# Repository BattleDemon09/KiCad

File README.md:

# KiCad
KiCad Schematics and PCBs

Please save all KiCad work here in a relevant folder

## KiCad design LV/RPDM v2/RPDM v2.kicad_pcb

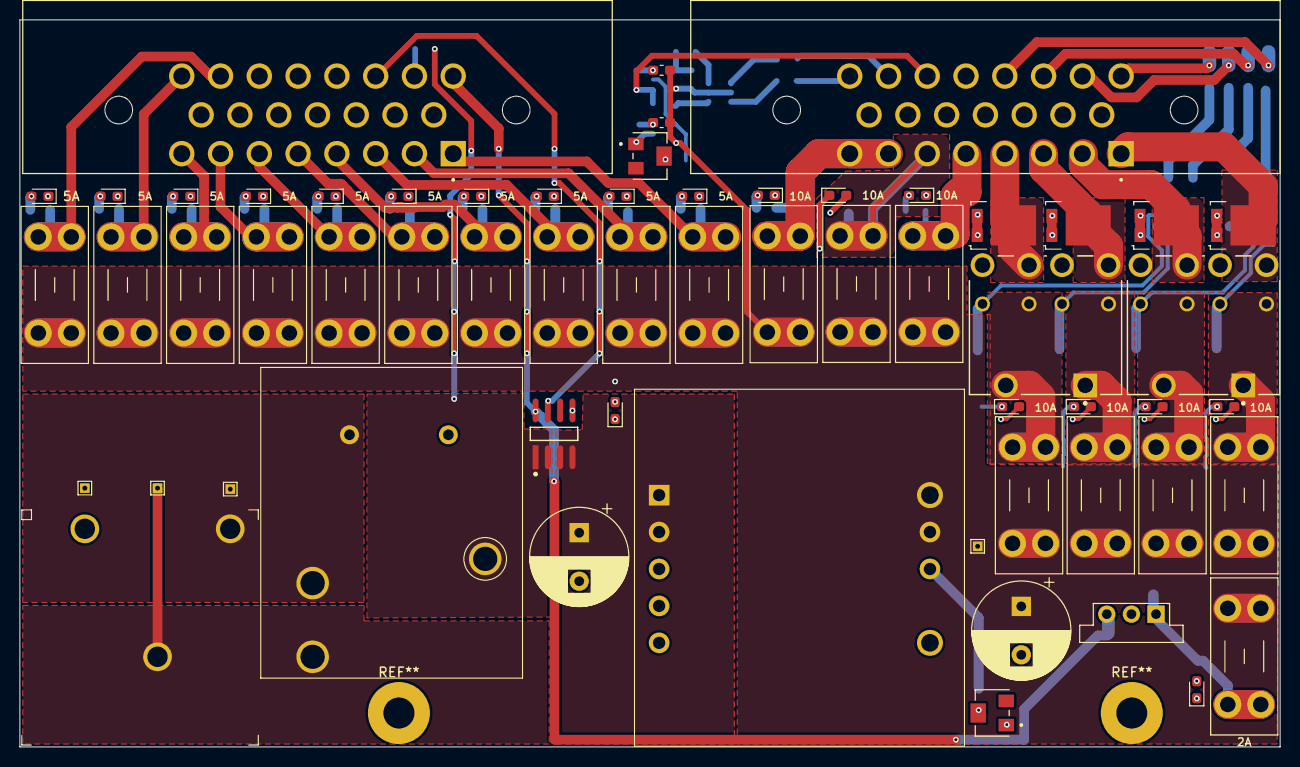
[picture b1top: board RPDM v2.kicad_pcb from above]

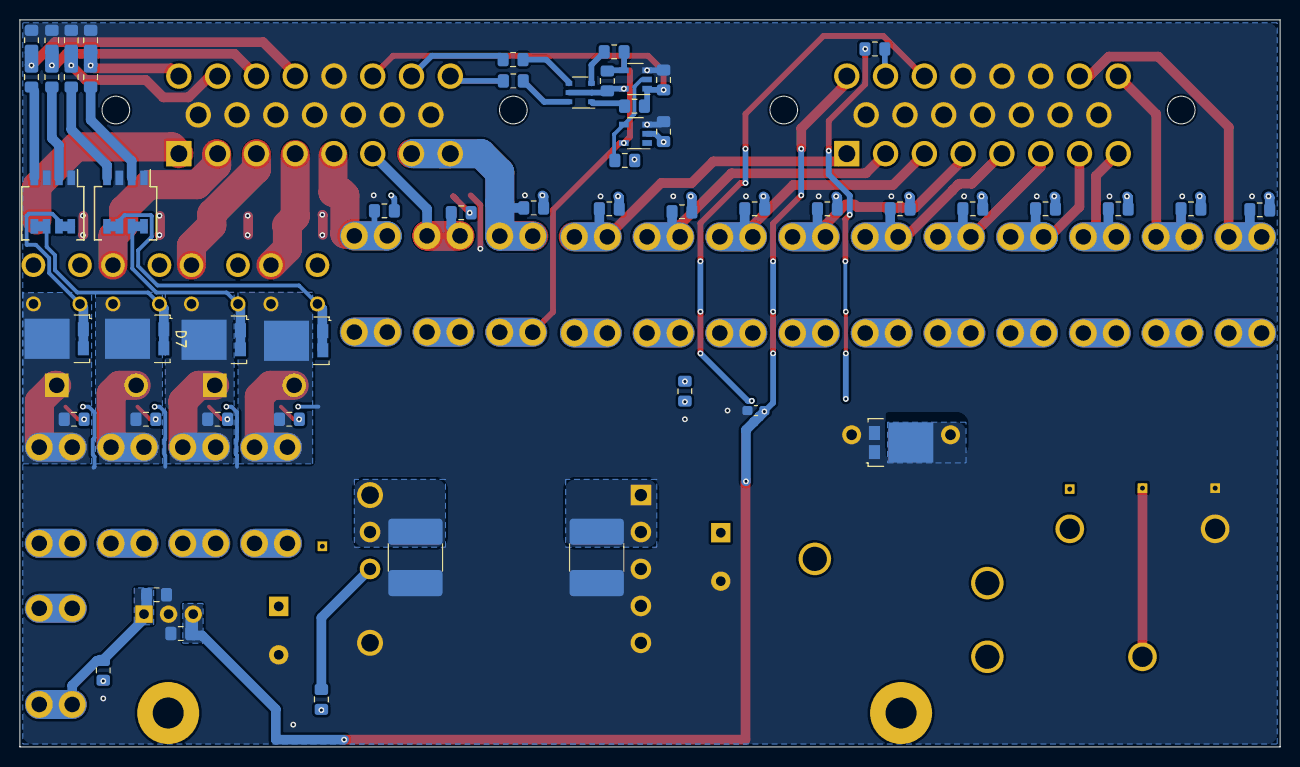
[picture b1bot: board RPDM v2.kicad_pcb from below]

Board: 2 copper layers, 130.0 x 75.0 mm, 112 parts (52 on the bottom side), 75 nets.

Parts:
C1, C3, C6: 0.1µF; C_0603_1608Metric_Pad1.05x0.95mm_HandSolder
C2: 1uF; C_0805_2012Metric_Pad1.15x1.40mm_HandSolder
C4, C5: 22µF; C_0805_2012Metric_Pad1.15x1.40mm_HandSolder
C7: 330µF; CP_Radial_D10.0mm_P5.00mm
C8, C9: 22µF; C_Murata_KCM55
C10: 330uF; CP_Radial_D10.0mm_P5.00mm
D1, D2, D3, D4, D5, D6, D7, D8, D30: D_Schottky_Flyback; TO-277_FSV10150V
D9, D10, D11, D12, D13, D14, D15, D16, D17, D18, D19, D20, D21, D22, D23, D24, D25, D26: OK_LED; D_0603_1608Metric_Pad1.05x0.95mm_HandSolder
D29: PWR_ON_LED; D_0603_1608Metric_Pad1.05x0.95mm_HandSolder
F1, F2, F3, F4, F5, F6, F7, F8, F9, F10, F11, F12, F13, F14, F15, F16, F17, F18: Fuse; Keystone_3568
J1: 24V_IN; EB167A-03-M
J2: 1-770669-1; TE_1-770669-1
J3: 776180-1; TE_1-770669-1
K1, K2: G8NW; Omron-G8NW-2L-AS_SK-MFG
K3: J115F; CIT_J115F1
Q1: Q_Dual_PMOS; TSOP-6_1.65x3.05mm_P0.95mm
Q2, Q3: Q_Dual_NMOS; Diodes_SO-8_5.3x6.2mm_P1.27mm
R1, R2, R3, R8, R10, R12, R14: 100k; R_0805_2012Metric_Pad1.15x1.40mm_HandSolder
R4, R5, R9, R11, R13, R15, R37: 470; R_0805_2012Metric_Pad1.15x1.40mm_HandSolder
R6, R7, R16, R17, R18, R19, R20, R21, R22, R23, R24, R25, R26, R27, R28, R29, R30, R31, R32, R33, R36, R38: 10k; R_0805_2012Metric_Pad1.15x1.40mm_HandSolder
RV1: 100k; TRIM_3214W
RV2: 1k; TRIM_3214W
TP1: GND Test Point; TestPoint_THTPad_1.0x1.0mm_Drill0.5mm
TP2: Ext. power test point; TestPoint_THTPad_1.0x1.0mm_Drill0.5mm
TP3: Battery test point; TestPoint_THTPad_1.0x1.0mm_Drill0.5mm
TP4: TestPoint; TestPoint_THTPad_1.0x1.0mm_Drill0.5mm
U1: BU4S584G2; SSOP-5_ROHM
U2: BU4S11G2; SSOP-5_ROHM
U3: OKI-78SR-5_1.5-W36-C; Converter_DCDC_muRata_OKI-78SR_Vertical
U4: ACS71240; Allegro_MicroSystems_LLC-LCB-8-0-0-IPC_A
U5: i7A24045A033V-001-R; i7A24045A033V

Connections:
/5V: C5.1, C6.1, J3.16, U3.3, U4.8
/5V_DCDC: C4.1, F8.2, R23.2, U3.1
/24_DCDC_IN: C7.1, C8.1, U4.3, U4.4, U5.1, U5.9
/24_ISENSE_IN: K3.1, R36.1, U4.1, U4.2
/+24V_BATT: J1.2, K3.3, TP2.1
/+24V_EXT: D30.3, J1.3, K3.4, K3.5, TP3.1
/ACCUMULATOR: F12.2, J3.4, R25.2
/ACC_FANS: F7.2, J2.7, J2.8, R22.2
/BATT_I: J3.18, U4.7
/BATT_V: J3.17, R36.2
/BMS_DATALOGGER: F13.2, J3.5, R28.2
/BRAKE_LIGHT: F17.2, J3.23, R32.2
/FPDM: F9.2, J3.1, R26.2
/HV_DIST: F14.2, J3.6, R29.2
/INTERLOCK: F15.2, J3.7, R30.2
/MOTOR_CONTROLLER_1: F10.2, J3.2, R27.2
/MOTOR_CONTROLLER_2: F11.2, J3.3, R24.2
/PDOC_12V: F18.2, J3.22, R33.2
/PUMPS: D4.3, J2.4, K1.8
/PUMP_1_Trigger: J2.17, R10.1, R11.2
/RAD_FANS: D2.3, J2.3, K1.3
/RAD_FAN_Trigger: J2.16, R8.1, R9.2
/RELAY_1: D5.3, F1.2, K2.1, K2.2, R16.2
/RELAY_2: D7.3, F2.2, K2.6, K2.7, R17.2
/RELAY_3: D1.3, F3.2, K1.1, K1.2, R18.2
/RELAY_4: D3.3, F4.2, K1.6, K1.7, R19.2
/SPARE_FUSE_1: F5.2, J2.5, R20.2
/SPARE_FUSE_2: F6.2, J2.6, R21.2
/SPARE_RELAY_1: D6.3, J2.1, K2.3
/SPARE_RELAY_2: D8.3, J2.2, K2.8
/SPARE_Trigger_1: J2.18, R12.1, R13.2
/SPARE_Trigger_2: J2.19, R14.1, R15.2
/TSAL_Green: J2.23, R7.1
/TSAL_PWR: F16.2, J3.8, R31.2
/TSAL_Red: J2.22, R6.1
/TSAT: J2.21, R3.2, R5.2, U2.1
/alt TSAL Logic/NAND_Out: R2.1, R4.2, U2.4
GND: C1.2, C2.2, C3.2, C4.2, C5.2, C6.2, C7.2, C8.2, C9.2, C10.2, D2.1, D2.2, D4.1, D4.2, D6.1, D6.2, D8.1, D8.2, D9.1, D10.1, D11.1, D12.1, D13.1, D14.1, D15.1, D16.1, D17.1, D18.1, D19.1, D20.1, D21.1, D22.1, D23.1, D24.1, D25.1, D26.1, D29.1, D30.1, D30.2, J1.1, J2.9, J2.10, J2.11, J2.12, J2.13, J2.14, J2.15, J2.20, J3.9, J3.10, J3.11, J3.12, J3.13, J3.14, J3.15, J3.19, J3.20, J3.21, K3.2, Q2.1, Q2.3, Q3.1, Q3.3, R3.1, R8.2, R10.2, R12.2, R14.2, RV2.1, TP1.1, U1.3, U2.3, U3.2, U4.5, U5.2, U5.3, U5.4, U5.10
unnamed: C2.1, RV1.1, U1.2
unnamed: D1.1, D1.2, K1.5, Q2.7, Q2.8
unnamed: D3.1, D3.2, K1.10, Q2.5, Q2.6
unnamed: D5.1, D5.2, K2.5, Q3.7, Q3.8
unnamed: D7.1, D7.2, K2.10, Q3.5, Q3.6
unnamed: D9.2, R16.1
unnamed: D10.2, R17.1
unnamed: D11.2, R18.1
unnamed: D12.2, R19.1
unnamed: D13.2, R20.1
unnamed: D14.2, R21.1
unnamed: D15.2, R22.1
unnamed: D16.2, R23.1
unnamed: D17.2, R24.1
unnamed: D18.2, R25.1
unnamed: D19.2, R26.1
unnamed: D20.2, R27.1
unnamed: D21.2, R28.1
unnamed: D22.2, R29.1
unnamed: D23.2, R30.1
unnamed: D24.2, R31.1
unnamed: D25.2, R32.1
unnamed: D26.2, R33.1
unnamed: D29.2, R38.2
unnamed: Q1.1, R5.1
unnamed: Q1.3, R4.1
unnamed: Q1.4, R6.2
unnamed: Q1.6, R7.2
unnamed: Q2.2, R9.1
unnamed: Q2.4, R11.1
unnamed: Q3.2, R13.1
unnamed: Q3.4, R15.1
unnamed: R1.1, U1.4, U2.2
unnamed: R1.2, RV1.2
unnamed: R37.1, U5.6
unnamed: R37.2, RV2.2
VCC: C1.1, C3.1, C9.1, C10.1, F1.1, F2.1, F3.1, F4.1, F5.1, F6.1, F7.1, F8.1, F9.1, F10.1, F11.1, F12.1, F13.1, F14.1, F15.1, F16.1, F17.1, F18.1, Q1.2, Q1.5, R2.2, R38.1, TP4.1, U1.5, U2.5, U5.7, U5.8

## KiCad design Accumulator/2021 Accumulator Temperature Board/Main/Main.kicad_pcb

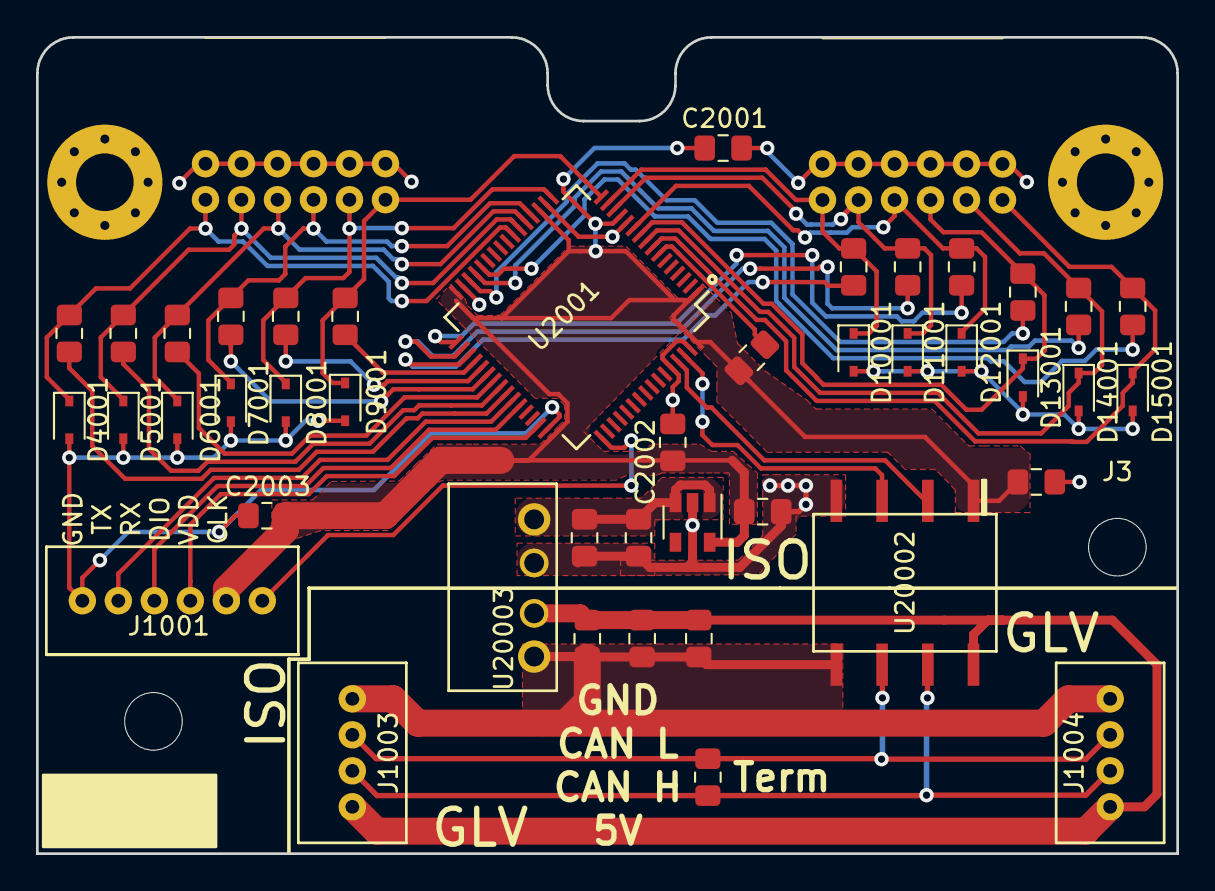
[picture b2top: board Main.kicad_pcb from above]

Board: 2 copper layers, 63.4 x 45.4 mm, 49 parts (0 on the bottom side), 38 nets.

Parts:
C2001, C2002, C2003, C3001, C3002, C20001, C20002, C20003, C20004: 100nF; C_0805_2012Metric_Pad1.15x1.40mm_HandSolder
C20005: 1uF; C_0805_2012Metric_Pad1.15x1.40mm_HandSolder
D4001, D5001, D6001, D7001, D8001, D9001, D10001, D11001, D12001, D13001, D14001, D15001: BZX84C3V6LFHT116; D_SOD-323
J1, J2: Conn_02x06_Odd_Even; S12B-PHDSS
J3, J1005: M3; MountingHole_3.2mm_M3
J1001: Conn_01x06; B06B-PASK
J1002, J1006: M3; MountingHole_3.2mm_M3_Pad_Via
J1003, J1004: Conn_01x04; B04B-PASK
R1005: 120R; R_0805_2012Metric_Pad1.15x1.40mm_HandSolder
R2001: 10k; R_0805_2012Metric_Pad1.15x1.40mm_HandSolder
R4001, R5001, R6001, R7001, R8001, R9001, R10001, R11001, R12001, R13001, R14001, R15001: 1k; R_0805_2012Metric_Pad1.15x1.40mm_HandSolder
U2001: STM32F072R8Tx; LQFP-64_10x10mm_P0.5mm
U3001: LP2985-3.3; SOT-23-5
U20002: ISO1050; ISO1050DUB
U20003: RFM-0505S

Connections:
/CAN Interface/CAN_5V: C20003.1, C20004.1, C20005.1, J1003.4, J1004.1, U20002.8, U20003.2
/CAN Interface/CAN_GND: C20003.2, C20004.2, C20005.2, J1003.1, J1004.4, U20002.5, U20003.1
/CAN Interface/CAN_H: J1003.3, J1004.2, R1005.1, U20002.7
/CAN Interface/CAN_L: J1003.2, J1004.3, R1005.2, U20002.6
/CAN Interface/CAN_RX: U2001.61, U20002.2
/CAN Interface/CAN_TX: U2001.62, U20002.3
/MUX Interface/ADC_0: D4001.1, J1.1, R4001.2, U2001.23
/MUX Interface/ADC_1: D5001.1, J1.3, R5001.2, U2001.22
/MUX Interface/ADC_2: D6001.1, J1.5, R6001.2, U2001.21
/MUX Interface/ADC_3: D7001.1, J1.7, R7001.2, U2001.20
/MUX Interface/ADC_4: D8001.1, J1.9, R8001.2, U2001.17
/MUX Interface/ADC_5: D9001.1, J1.11, R9001.2, U2001.16
/MUX Interface/ADC_6: D10001.1, J2.1, R10001.2, U2001.15
/MUX Interface/ADC_7: D11001.1, J2.3, R11001.2, U2001.14
/MUX Interface/ADC_8: D12001.1, J2.5, R12001.2, U2001.11
/MUX Interface/ADC_9: D13001.1, J2.7, R13001.2, U2001.10
/MUX Interface/ADC_10: D14001.1, J2.9, R14001.2, U2001.9
/MUX Interface/ADC_11: D15001.1, J2.11, R15001.2, U2001.8
/MUX Interface/PU_0: R4001.1, U2001.41
/MUX Interface/PU_1: R5001.1, U2001.40
/MUX Interface/PU_2: R6001.1, U2001.39
/MUX Interface/PU_3: R7001.1, U2001.38
/MUX Interface/PU_4: R8001.1, U2001.37
/MUX Interface/PU_5: R9001.1, U2001.36
/MUX Interface/PU_6: R10001.1, U2001.35
/MUX Interface/PU_7: R11001.1, U2001.34
/MUX Interface/PU_8: R12001.1, U2001.33
/MUX Interface/PU_9: R13001.1, U2001.30
/MUX Interface/PU_10: R14001.1, U2001.29
/MUX Interface/PU_11: R15001.1, U2001.28
/STM32F072/SWCLK: J1001.6, U2001.49
/STM32F072/SWDIO: J1001.4, U2001.46
/STM32F072/UART_RX: J1001.3, U2001.43
/STM32F072/UART_TX: J1001.2, U2001.42
GND: C2001.2, C2002.2, C2003.2, C3001.2, C3002.2, C20001.2, C20002.2, D4001.2, D5001.2, D6001.2, D7001.2, D8001.2, D9001.2, D10001.2, D11001.2, D12001.2, D13001.2, D14001.2, D15001.2, J1.2, J1.4, J1.6, J1.8, J1.10, J1.12, J2.2, J2.4, J2.6, J2.8, J2.10, J2.12, J1001.1, U2001.12, U2001.18, U2001.31, U2001.47, U2001.60, U2001.63, U3001.2, U20002.4, U20003.3
unnamed: C3001.1, C3002.1, U3001.1, U3001.3, U20003.4
unnamed: R2001.2, U2001.7
VDD: C2001.1, C2002.1, C2003.1, C20001.1, C20002.1, J1001.5, R2001.1, U2001.1, U2001.13, U2001.19, U2001.32, U2001.48, U2001.64, U3001.5, U20002.1

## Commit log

2021-06-26 Started on RPDM
2021-06-26 Moved files
2021-06-26 added .gitignore
2021-06-26 gitignore changed
2021-06-28 RPDM v2 nearly done
2021-06-29 RPDM update
2021-07-01 rpdm
2021-07-03 Created a new folder for Accumulator files and added the Thermoboard KiCAD files to it.
2021-07-06 rPDM - Started on board layout
2021-07-07 rpdm, libraries cleanup
2021-07-10 Changes to Thermoboard
    Disconnected mounting holes from GND, changed Zener package to hand-soldering.
2021-07-13 Changes to Thermoboard Mounting
2021-07-13 Harness Test Upload
2021-07-14 RPDM nearly finished
2021-07-15 Added to LV Harness
2021-07-16 Changes to LV Harness Schematic
2021-07-17 Added new files to be used for 2021 LV Harness
2021-07-17 started LV Harness
2021-07-17 harness
2021-07-17 Started Projects for LV Harness Pinouts
2021-07-17 Changes to LV Harness Folders
2021-07-21 Motor Controller Pinouts labelled
    The pins have been labelled
